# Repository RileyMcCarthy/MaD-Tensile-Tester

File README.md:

# Low Modulus High Speed Tensile Testing Machine

## Purpose

Function as a relatively low cost (< $4,000), portable, spray resistant, user modifiable, open-source uniaxial tensile testing machine for low modulus elastomeric and biologic materials. 

## Physical Specifications

- Strain Rate 0 – 2 m/s

- Force Measurement Range 1 – 10 N

- Gauge Length 10 – 150 mm

- Strain Length 0 – 500 mm

- Data generation rate 1000 sps

## Power Up Sequence

1. Turning on the mains inlet power switch will power the motion control electronics including the “inboard” power on the tensile board 

2. Depressing the on button of the momentary on-off button pair will apply DC power to the machine status switches and ESD chain circuit. 

3. Release of the ESD switch which will apply AC power to the servo controller. 

4. When machine operational and safety criteria are met, motion is affected through operator actuation of the reset function with a control panel and touch screen. 

5. The power down sequence is the reverse of the power up sequence with the off button of the momentary on-off button pair being pressed to remove DC power.

## Operation

The machine state machine operates in three main states with corresponding parameters; 

1. Self Check
- Charge Pump Activated (**ON**/OFF)
2. Machine Check
- Switched Power (**ON**/OFF)
- ESD Travel Limits (**OK**/UPPER FAULT/LOWER FAULT)
- ESD Switch (**ON**/OFF)
- Servo Ready (**YES**/NO)
- Servo Communicating (**YES**/NO)
- Force Gauge Ready (**YES**/NO)
3. Motion
- Mode (Manual or Test)
- Status (DISABLED, ENABLED, SAMPLE LIMIT, MACHINE LIMIT, FAULT)
- Condition (Length, Force, Tension, Compression, Upper Limit, Lower Limit, Door, Stopped, Moving)

## Manual Mode

Manual Operation Mode controls the motor based on user input. The user can selected from the following functions: Off, Incremental Jog, Continuous Jog, Move to Position, Handwheel Jog, Move to Home Position, Set or Move to a Gauge Length, Set or Move to a Force Level and Hold. 

## Test Mode 
Test Mode controls the motor automatically using the functions: Load, Run, Stop Test (Stop Tst) and Hold/Resume.  Motion Profiles are executed by the Run Function. 

** Documentation is a WIP **

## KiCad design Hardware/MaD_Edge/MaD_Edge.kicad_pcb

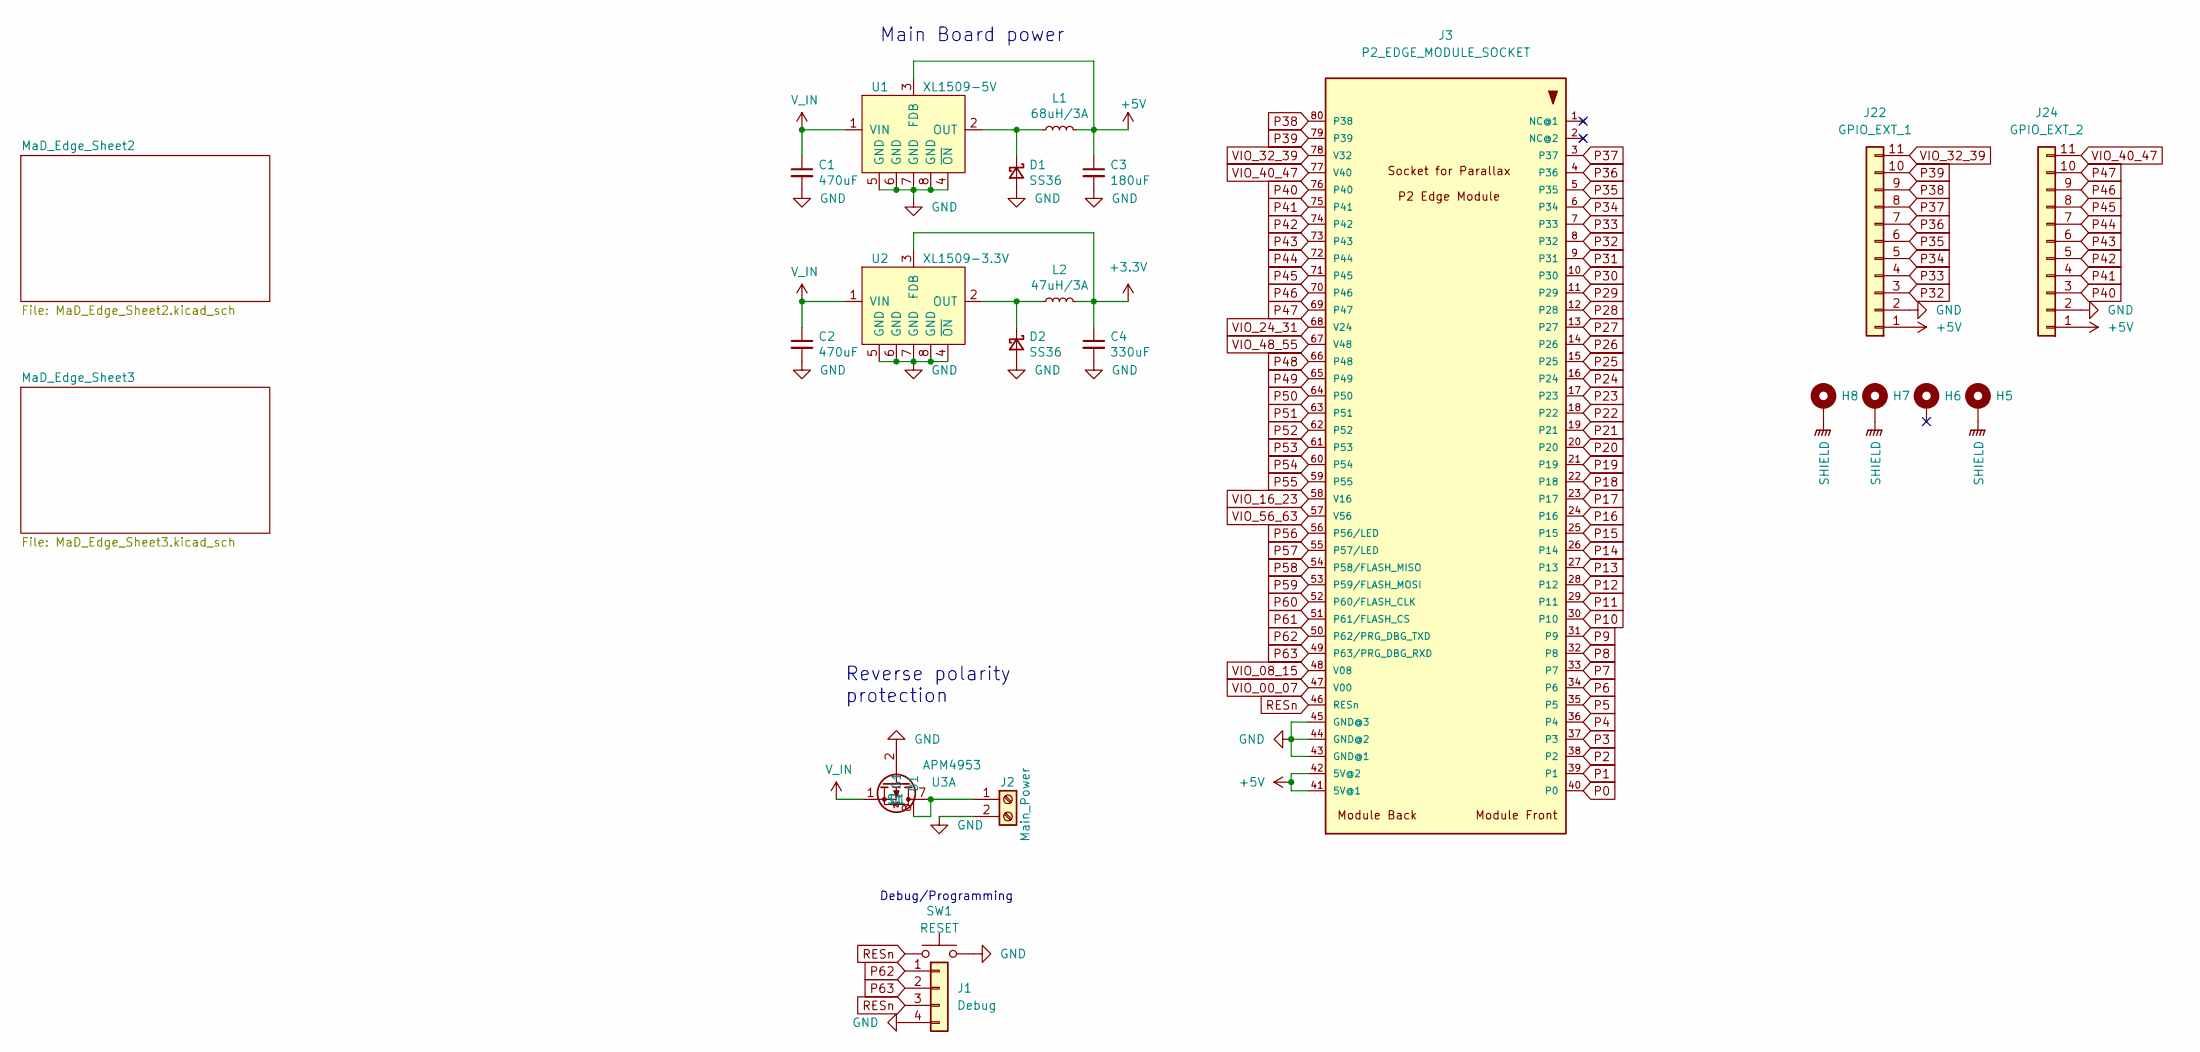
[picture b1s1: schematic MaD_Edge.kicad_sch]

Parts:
C1, C2: 470uF; C_Elec_10x10.2; Manufacturer_Part_Number EEH-ZS1E471P; DIGIKEY 10-EEH-ZS1E471PCT-ND
C3: 180uF; CP_Elec_8x6.9; Manufacturer_Part_Number 25SVPF180M; DIGIKEY P16510CT-ND
C4: 330uF; C_Elec_10x10.2; Manufacturer_Part_Number 25SVPF330M; DIGIKEY P16512CT-ND
D1, D2: SS36; D_SMC; Manufacturer_Part_Number SS36-E3/57T; DIGIKEY SS36-E3/57TGICT-ND
H5, H6, H7, H8: MountingHole_Pad; MountingHole_4mm_Pad; Manufacturer_Part_Number DNP; LCSC DNP
J1: Debug; PinHeader_1x04_P2.54mm_Vertical; Manufacturer_Part_Number DNP; LCSC DNP
J2: Main_Power; 705530106; Manufacturer_Part_Number 0705530106; DIGIKEY WM4153-ND
J3: P2_EDGE_MODULE_SOCKET; Card_Edge_SMT_VERT_1.27mm_80p; Manufacturer_Part_Number 450-00309; LCSC DNP
J22: GPIO_EXT_1; PinHeader_1x11_P1.27mm_Vertical; Manufacturer_Part_Number DNP; LCSC DNP
J24: GPIO_EXT_2; PinHeader_1x11_P1.27mm_Vertical; Manufacturer_Part_Number DNP; LCSC DNP
L1: 68uH/3A; L_10.4x10.4_H4.8; Manufacturer_Part_Number SRP1038A-470M; DIGIKEY SRP1038A-470MCT-ND
L2: 47uH/3A; L_10.4x10.4_H4.8; Manufacturer_Part_Number SLO1365H470MTT; LCSC C149548
SW1: RESET; SW_SPST_PTS645; manufacturer_part_numbe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 PTS645VK31LFS; LCSC C2804591
U1: XL1509-5V; SOP-8_3.9x4.9mm_P1.27mm; Manufacturer_Part_Number XL1509-5.0E1; LCSC C61063
U2: XL1509-3.3V; SOP-8_3.9x4.9mm_P1.27mm; Manufacturer_Part_Number XL1509-3.3E1; LCSC C74193
U3: APM4953; SOP-8_3.9x4.9mm_P1.27mm; Manufacturer_Part_Number APM4953KC-TRG; LCSC C20897

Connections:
+3.3V: C4.1, L2.2, U2.3 (FDB); also elsewhere on the board
+5V: C3.1, J3.41 (5V@1), J3.42 (5V@2), J22.1, J24.1, L1.2, U1.3 (FDB); also elsewhere on the board
GND: C1.2, C2.2, C3.2, C4.2, D1.2 (A), D2.2 (A), J1.4, J2.2, J3.43 (GND@1), J3.44 (GND@2), J3.45 (GND@3), J22.2, J24.2, SW1.2, U1.4 (~ON), U1.5 (GND), U1.6 (GND), U1.7 (GND), U1.8 (GND), U2.4 (~ON), U2.5 (GND), U2.6 (GND), U2.7 (GND), U2.8 (GND), U3.2 (G1); also elsewhere on the board
unnamed: D1.1 (K), L1.1, U1.2 (OUT)
unnamed: D2.1 (K), L2.1, U2.2 (OUT)
unnamed: J2.1, U3.7 (D1), U3.8 (D1)
P0: J3.40 (P0); also elsewhere on the board
P1: J3.39 (P1); also elsewhere on the board
P2: J3.38 (P2); also elsewhere on the board
P3: J3.37 (P3); also elsewhere on the board
P4: J3.36 (P4); also elsewhere on the board
P5: J3.35 (P5); also elsewhere on the board
P6: J3.34 (P6); also elsewhere on the board
P7: J3.33 (P7); also elsewhere on the board
P8: J3.32 (P8); also elsewhere on the board
P9: J3.31 (P9); also elsewhere on the board
P10: J3.30 (P10); also elsewhere on the board
P11: J3.29 (P11); also elsewhere on the board
P12: J3.28 (P12); also elsewhere on the board
P13: J3.27 (P13); also elsewhere on the board
P14: J3.26 (P14); also elsewhere on the board
P15: J3.25 (P15); also elsewhere on the board
P16: J3.24 (P16); also elsewhere on the board
P17: J3.23 (P17); also elsewhere on the board
P18: J3.22 (P18); also elsewhere on the board
P19: J3.21 (P19); also elsewhere on the board
P20: J3.20; also elsewhere on the board
P21: J3.19 (P21); also elsewhere on the board
P22: J3.18 (P22); also elsewhere on the board
P23: J3.17 (P23); also elsewhere on the board
P24: J3.16 (P24); also elsewhere on the board
P25: J3.15 (P25); also elsewhere on the board
P26: J3.14 (P26); also elsewhere on the board
P27: J3.13 (P27); also elsewhere on the board
P28: J3.12 (P28); also elsewhere on the board
P29: J3.11 (P29)
P30: J3.10 (P30)
P31: J3.9 (P31)
P32: J3.8 (P32), J22.3
P33: J3.7 (P33), J22.4
P34: J3.6 (P34), J22.5
P35: J3.5 (P35), J22.6
P36: J3.4 (P36), J22.7
P37: J3.3 (P37), J22.8
P38: J3.80 (P38), J22.9
P39: J3.79 (P39), J22.10
P40: J3.76 (P40), J24.3
P41: J3.75 (P41), J24.4
P42: J3.74 (P42), J24.5
P43: J3.73 (P43), J24.6
P44: J3.72 (P44), J24.7
P45: J3.71 (P45), J24.8
P46: J3.70 (P46), J24.9
P47: J3.69 (P47), J24.10
P48: J3.66 (P48)
P49: J3.65 (P49)
P50: J3.64 (P50)
P51: J3.63 (P51)
P52: J3.62 (P52); also elsewhere on the board
P53: J3.61 (P53); also elsewhere on the board
P54: J3.60 (P54); also elsewhere on the board
P55: J3.59 (P55); also elsewhere on the board
P56: J3.56 (P56/LED)
P57: J3.55 (P57/LED)
P58: J3.54 (P58/FLASH_MISO)
P59: J3.53 (P59/FLASH_MOSI)
P60: J3.52 (P60/FLASH_CLK)
P61: J3.51 (P61/FLASH_CS)
P62: J1.1, J3.50 (P62/PRG_DBG_TXD)
P63: J1.2, J3.49 (P63/PRG_DBG_RXD)
RESn: J1.3, J3.46 (RESn), SW1.1
SHIELD: H5.1, H7.1, H8.1; also elsewhere on the board
VIO_00_07: J3.47 (V00)
VIO_08_15: J3.48 (V08)
VIO_16_23: J3.58 (V16); also elsewhere on the board
VIO_24_31: J3.68 (V24)
VIO_32_39: J3.78 (V32), J22.11
VIO_40_47: J3.77 (V40), J24.11
VIO_48_55: J3.67 (V48)
VIO_56_63: J3.57 (V56)
V_IN: C1.1, C2.1, U1.1 (VIN), U2.1 (VIN), U3.1 (S1)

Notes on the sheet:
Debug/Programming
Main Board power
Reverse polarity protection

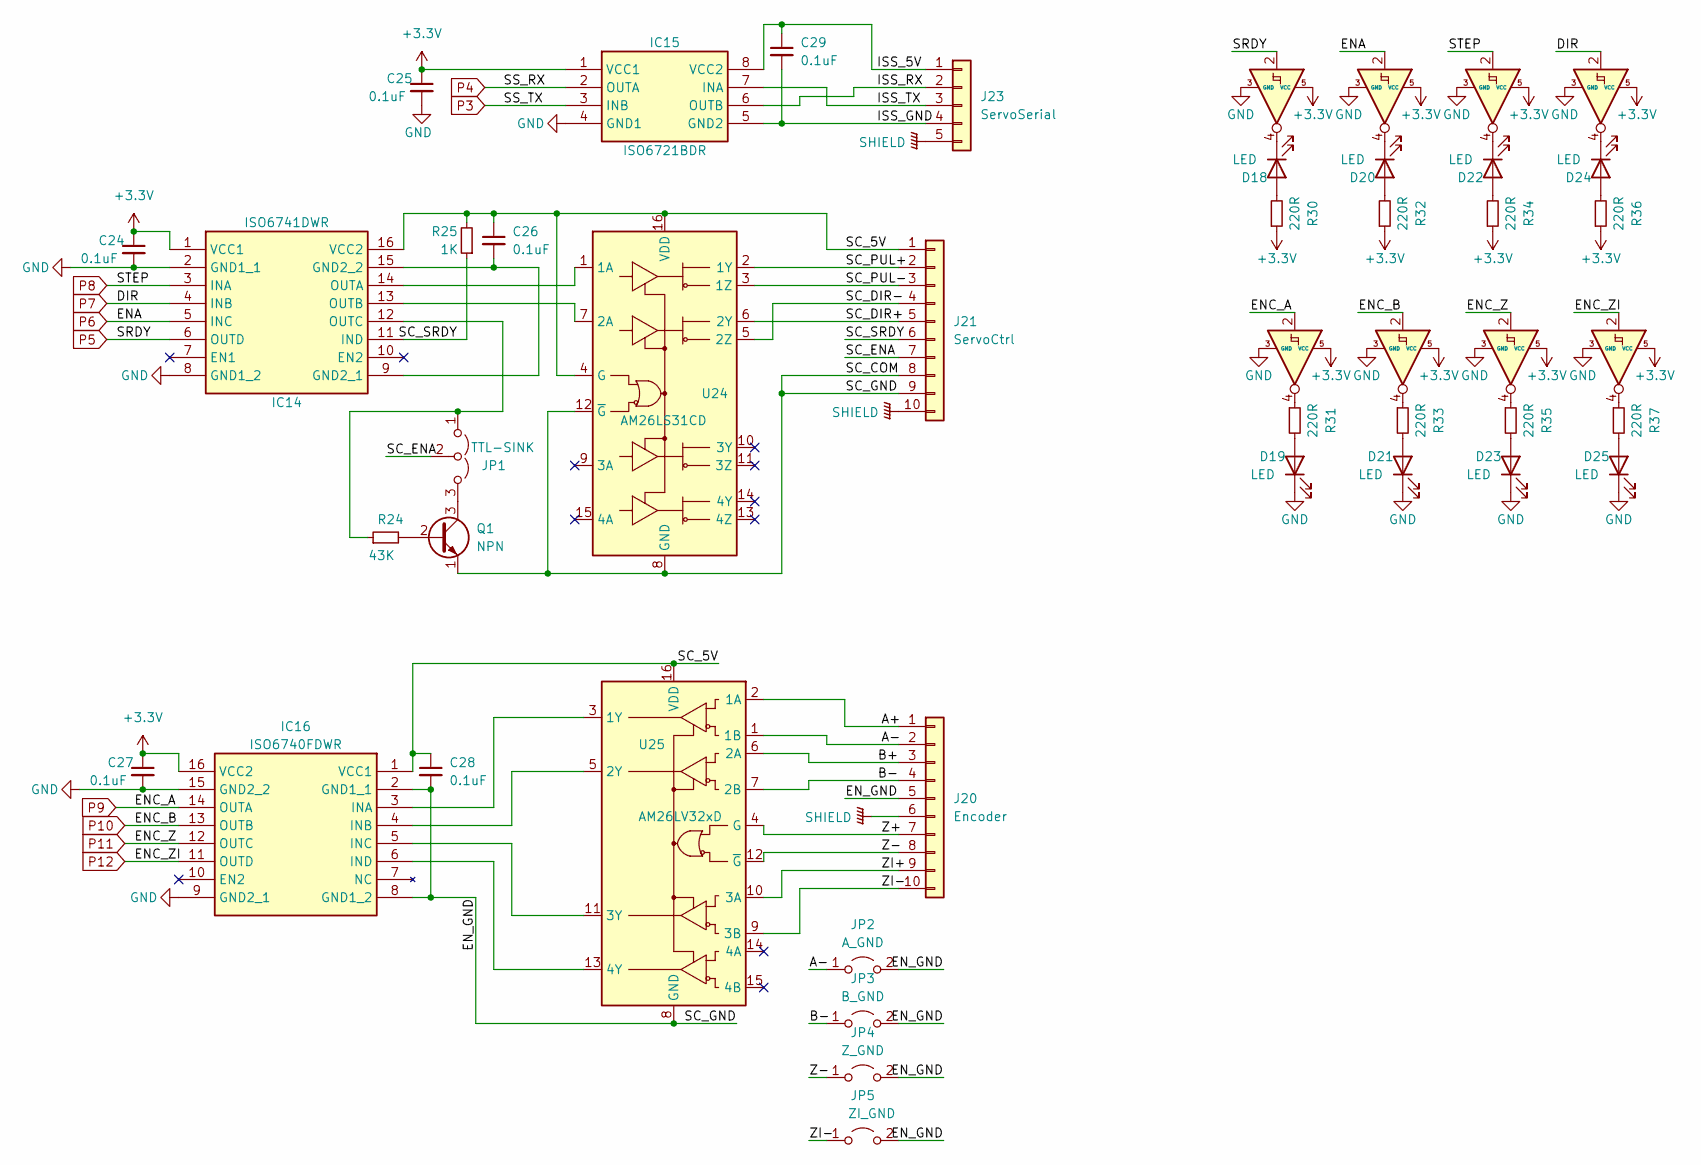
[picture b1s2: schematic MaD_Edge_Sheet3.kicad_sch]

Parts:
C24, C25, C26, C27, C28, C29: 0.1uF; C_0603_1608Metric; Manufacturer_Part_Number CL05A104KA5NNNC; DIGIKEY 1276-1043-1-ND
D18, D19, D20, D21, D22, D23, D24, D25: LED; LED_0603_1608Metric; Manufacturer_Part_Number LTST-C190KGKT; DIGIKEY 160-1435-1-ND
IC14: ISO6741DWR; SOIC127P1030X265-16N; Manufacturer_Part_Number ISO6741DWR; DIGIKEY 296-ISO6741DWRCT-ND
IC15: ISO6721BDR; SOIC127P600X175-8N; Manufacturer_Part_Number ISO6721BDR; DIGIKEY 296-ISO6721BDRCT-ND
IC16: ISO6740FDWR; SOIC127P1030X265-16N; Manufacturer_Part_Number ISO6740DWR; DIGIKEY 296-ISO6740DWRCT-ND
J20: Encoder; Molex_Micro-Fit_3.0_43045-1015_2x05_P3.00mm_Vertical; Manufacturer_Part_Number 0430451015; DIGIKEY WM14304CT-ND
J21: ServoCtrl; Molex_Micro-Fit_3.0_43045-1015_2x05_P3.00mm_Vertical; Manufacturer_Part_Number 0430451015; DIGIKEY WM14304CT-ND
J23: ServoSerial; Molex_Micro-Fit_3.0_43650-0521_1x05_P3.00mm_Vertical; Manufacturer_Part_Number 0436500521; DIGIKEY WM14316CT-ND
JP1: TTL-SINK; PinHeader_1x03_P2.54mm_Vertical; manufacturer_part_numbe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 PZ254V-11-03P; LCSC C2937625
JP2: A_GND; PinHeader_1x02_P2.54mm_Vertical; manufacturer_part_numbe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 PZ254V-11-02P; LCSC C492401
JP3: B_GND; PinHeader_1x02_P2.54mm_Vertical; manufacturer_part_numbe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 PZ254V-11-02P; LCSC C492401
JP4: Z_GND; PinHeader_1x02_P2.54mm_Vertical; manufacturer_part_numbe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 PZ254V-11-02P; LCSC C492401
JP5: ZI_GND; PinHeader_1x02_P2.54mm_Vertical; manufacturer_part_numbe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 PZ254V-11-02P; LCSC C492401
Q1: NPN; TSOT-23; Manufacturer_Part_Number MMBT3904-TP; LCSC C20526
R24: 43K; R_0603_1608Metric; manufacturer_part_numbe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 0603WAF4302T5E; LCSC C23172
R25: 1K; R_0603_1608Metric; manufacturer_part_numbe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 0603WAF1001T5E; LCSC C21190
R30, R31, R32, R33, R34, R35, R36, R37: 220R; R_0603_1608Metric; manufacturer_part_numbe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 0603WAF2200T5E; LCSC C22962
U24: AM26LS31CD; SOIC-16_3.9x9.9mm_P1.27mm; Manufacturer_Part_Number AM26LS31CD; LCSC C6179
U25: AM26LV32xD; SOIC-16_3.9x9.9mm_P1.27mm; Manufacturer_Part_Number AM26LS32CD; LCSC C524786
U27, U28, U29, U30, U31, U32, U33, U34: SN74LVC1G14DBV; SOT-23-5; Manufacturer_Part_Number SN74LVC1G14DBVT; LCSC C5250998

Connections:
+3.3V: C24.1, C25.1, C27.1, IC14.1 (VCC1), IC15.1 (VCC1), IC16.16 (VCC2), R30.1, R32.1, R34.1, R36.1, U27.5 (VCC), U28.5 (VCC), U29.5 (VCC), U30.5 (VCC), U31.5 (VCC), U32.5 (VCC), U33.5 (VCC), U34.5 (VCC); also elsewhere on the board
/MaD_Edge_Sheet3/A+: J20.1, U25.2 (1A)
/MaD_Edge_Sheet3/A-: J20.2, JP2.1 (A), U25.1 (1B)
/MaD_Edge_Sheet3/B+: J20.3, U25.6 (2A)
/MaD_Edge_Sheet3/B-: J20.4, JP3.1 (A), U25.7 (2B)
/MaD_Edge_Sheet3/EN_GND: C28.2, IC16.2 (GND1_1), IC16.8 (GND1_2), J20.5, J21.8, J21.9, JP2.2 (B), JP3.2 (B), JP4.2 (B), JP5.2 (B), Q1.1 (E), U24.8 (GND), U24.12 (~G), U25.8 (GND)
/MaD_Edge_Sheet3/ISS_5V: C29.1, IC15.8 (VCC2), J23.1
/MaD_Edge_Sheet3/ISS_GND: C29.2, IC15.5 (GND2), J23.4
/MaD_Edge_Sheet3/ISS_RX: IC15.6 (OUTB), J23.2
/MaD_Edge_Sheet3/ISS_TX: IC15.7 (INA), J23.3
/MaD_Edge_Sheet3/SC_5V: C26.1, C28.1, IC14.16 (VCC2), IC16.1 (VCC1), J21.1, R25.2, U24.4 (G), U24.16 (VDD), U25.16 (VDD)
/MaD_Edge_Sheet3/SC_DIR+: J21.5, U24.6 (2Y)
/MaD_Edge_Sheet3/SC_DIR-: J21.4, U24.5 (2Z)
/MaD_Edge_Sheet3/SC_ENA: J21.7, JP1.2 (C)
/MaD_Edge_Sheet3/SC_PUL+: J21.2, U24.2 (1Y)
/MaD_Edge_Sheet3/SC_PUL-: J21.3, U24.3 (1Z)
/MaD_Edge_Sheet3/SC_SRDY: IC14.11 (IND), J21.6, R25.1
/MaD_Edge_Sheet3/Z+: J20.7, U25.4 (G)
/MaD_Edge_Sheet3/Z-: J20.8, JP4.1 (A), U25.12 (~G)
/MaD_Edge_Sheet3/ZI+: J20.9, U25.10 (3A)
/MaD_Edge_Sheet3/ZI-: J20.10, JP5.1 (A), U25.9 (3B)
GND: C24.2, C25.2, C27.2, D19.1 (K), D21.1 (K), D23.1 (K), D25.1 (K), IC14.2 (GND1_1), IC14.8 (GND1_2), IC15.4 (GND1), IC16.9 (GND2_1), IC16.15 (GND2_2), U27.3 (GND), U28.3 (GND), U29.3 (GND), U30.3 (GND), U31.3 (GND), U32.3 (GND), U33.3 (GND), U34.3 (GND); also elsewhere on the board
unnamed: C26.2, IC14.9 (GND2_1), IC14.15 (GND2_2)
unnamed: D18.1 (K), U27.4
unnamed: D18.2 (A), R30.2
unnamed: D19.2 (A), R31.2
unnamed: D20.1 (K), U29.4
unnamed: D20.2 (A), R32.2
unnamed: D21.2 (A), R33.2
unnamed: D22.1 (K), U31.4
unnamed: D22.2 (A), R34.2
unnamed: D23.2 (A), R35.2
unnamed: D24.1 (K), U33.4
unnamed: D24.2 (A), R36.2
unnamed: D25.2 (A), R37.2
unnamed: IC14.12 (OUTC), JP1.1 (A), R24.1
unnamed: IC14.13 (OUTB), U24.7 (2A)
unnamed: IC14.14 (OUTA), U24.1 (1A)
unnamed: IC16.3 (INA), U25.3 (1Y)
unnamed: IC16.4 (INB), U25.5 (2Y)
unnamed: IC16.5 (INC), U25.11 (3Y)
unnamed: IC16.6 (IND), U25.13 (4Y)
unnamed: JP1.3 (B), Q1.3 (C)
unnamed: Q1.2 (B), R24.2
unnamed: R31.1, U28.4
unnamed: R33.1, U30.4
unnamed: R35.1, U32.4
unnamed: R37.1, U34.4
P3: IC15.3 (INB); also elsewhere on the board
P4: IC15.2 (OUTA); also elsewhere on the board
P5: IC14.6 (OUTD), U27.2; also elsewhere on the board
P6: IC14.5 (INC), U29.2; also elsewhere on the board
P7: IC14.4 (INB), U33.2; also elsewhere on the board
P8: IC14.3 (INA), U31.2; also elsewhere on the board
P9: IC16.14 (OUTA), U28.2; also elsewhere on the board
P10: IC16.13 (OUTB), U30.2; also elsewhere on the board
P11: IC16.12 (OUTC), U32.2; also elsewhere on the board
P12: IC16.11 (OUTD), U34.2; also elsewhere on the board
SHIELD: J20.6, J21.10, J23.5; also elsewhere on the board

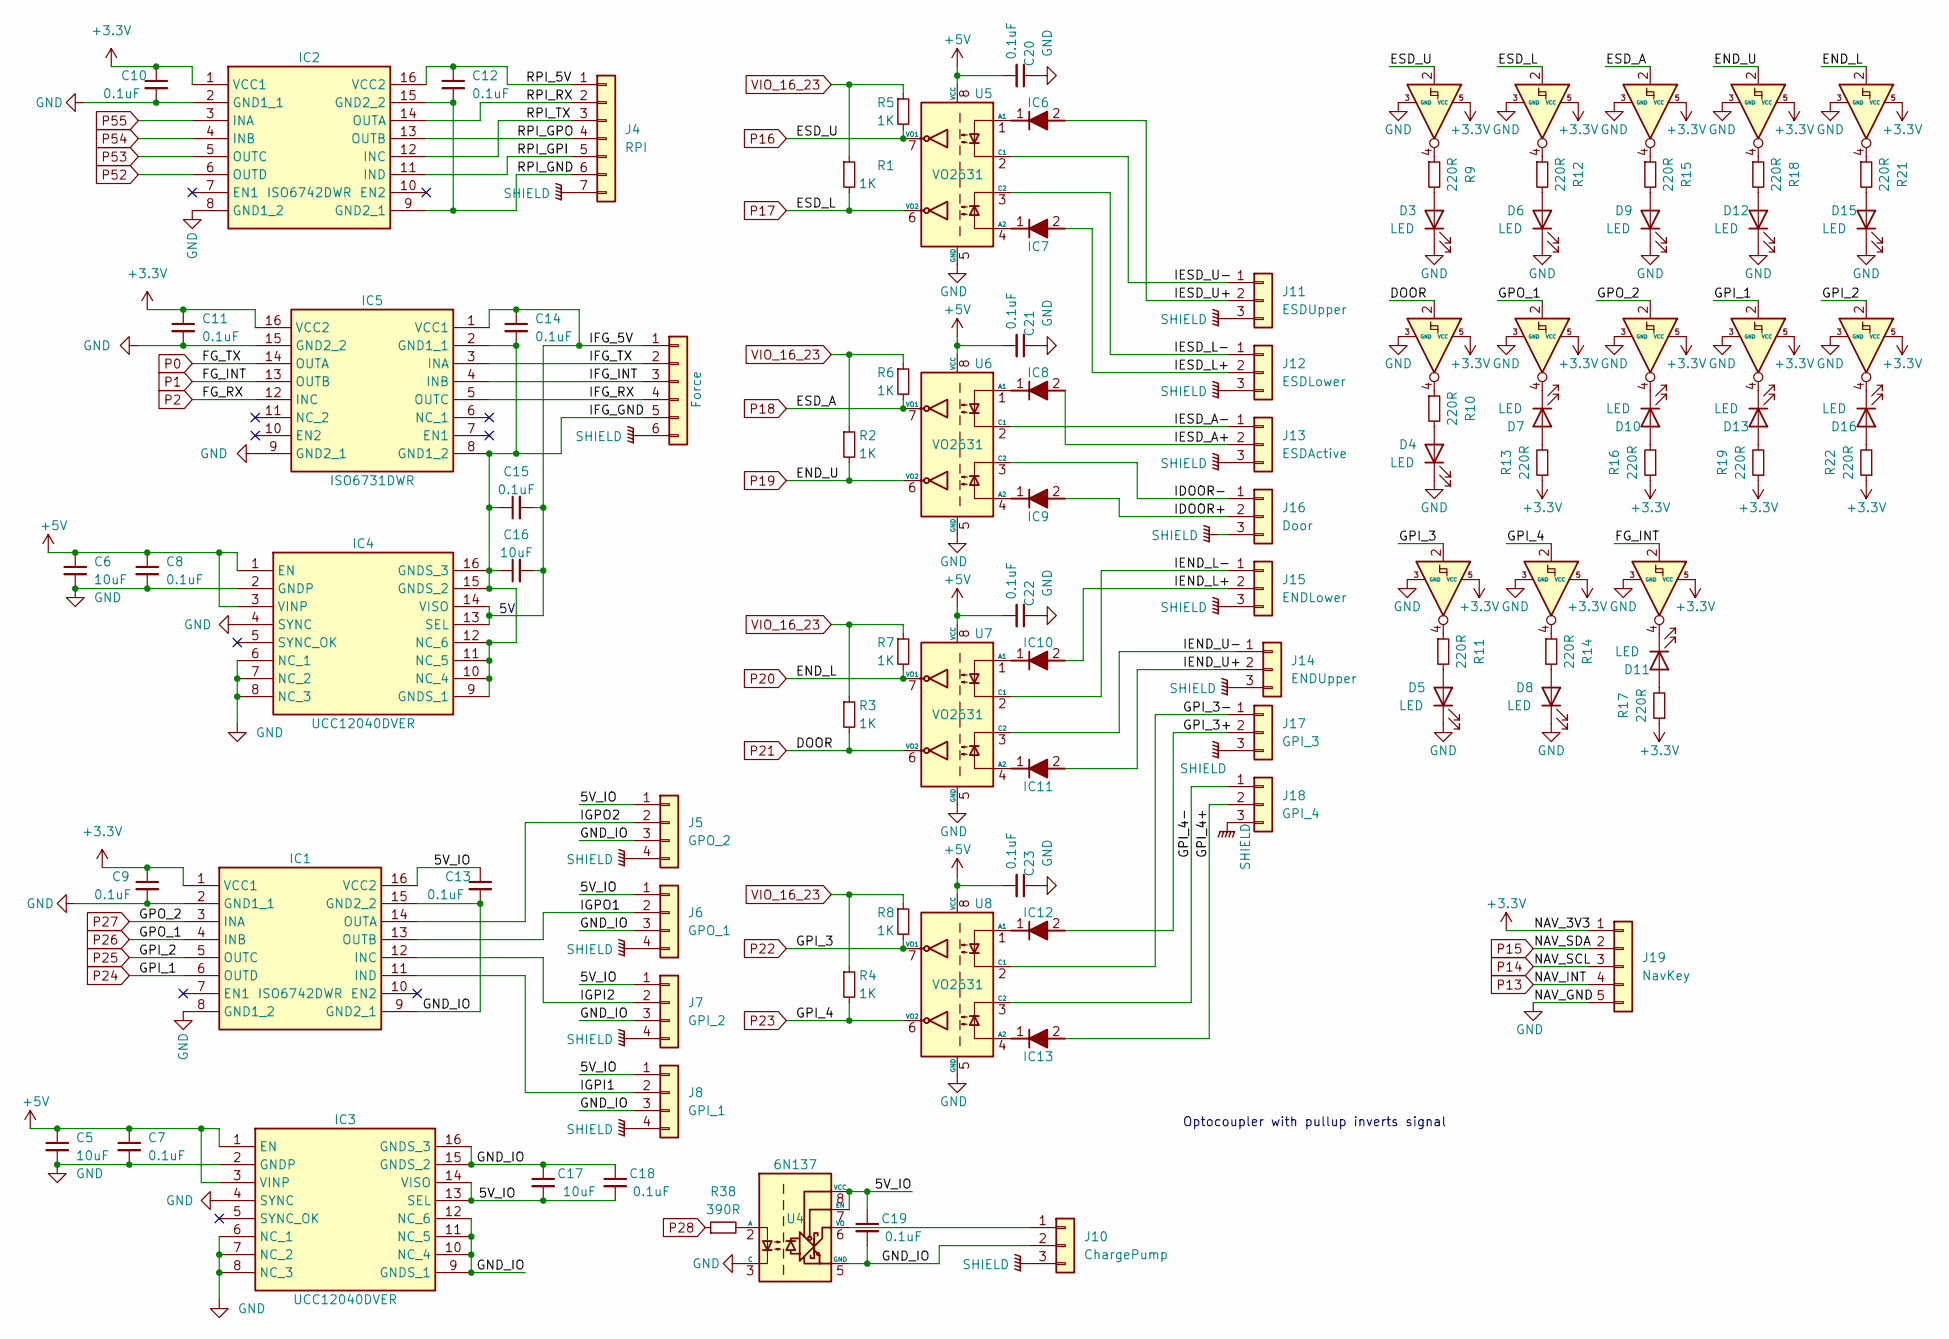
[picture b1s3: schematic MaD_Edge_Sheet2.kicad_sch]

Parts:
C5, C6, C16, C17: 10uF; C_1206_3216Metric; Manufacturer_Part_Number CL31A106MAHNNNE; DIGIKEY 1276-1181-1-ND
C7, C8, C9, C10, C11, C12, C13, C14, C15, C18, C19, C20, C21, C22, C23: 0.1uF; C_0603_1608Metric; Manufacturer_Part_Number CL05A104KA5NNNC; DIGIKEY 1276-1043-1-ND
D3, D4, D5, D6, D7, D8, D9, D10, D11, D12, D13, D15, D16: LED; LED_0603_1608Metric; Manufacturer_Part_Number LTST-C190KGKT; DIGIKEY 160-1435-1-ND
IC1, IC2: ISO6742DWR; SOIC127P1030X265-16N; Manufacturer_Part_Number ISO6742DWR; DIGIKEY 296-ISO6742DWRCT-ND
IC3, IC4: UCC12040DVER; SOIC127P1030X265-16N; Manufacturer_Part_Number UCC12040DVER; DIGIKEY 296-UCC12040DVERCT-ND
IC5: ISO6731DWR; SOIC127P1030X265-16N; Manufacturer_Part_Number ISO6731DWR; DIGIKEY 296-ISO6731DWRCT-ND
IC6, IC7, IC8, IC9, IC10, IC11, IC12, IC13: NSI50010YT1G; SOD3716X135N; Manufacturer_Part_Number NSI50010YT1G; DIGIKEY NSI50010YT1G
J4: RPI; Molex_Micro-Fit_3.0_43045-0618_2x03-1MP_P3.00mm_Vertical; Manufacturer_Part_Number 0430450618; DIGIKEY WM1803CT-ND
J5: GPO_2; Molex_Micro-Fit_3.0_43045-0415_2x02_P3.00mm_Vertical; Manufacturer_Part_Number 0430450415; DIGIKEY WM3251CT-ND
J6: GPO_1; Molex_Micro-Fit_3.0_43045-0415_2x02_P3.00mm_Vertical; Manufacturer_Part_Number 0430450415; DIGIKEY WM3251CT-ND
J7: GPI_2; Molex_Micro-Fit_3.0_43045-0415_2x02_P3.00mm_Vertical; Manufacturer_Part_Number 0430450415; DIGIKEY WM3251CT-ND
J8: GPI_1; Molex_Micro-Fit_3.0_43045-0415_2x02_P3.00mm_Vertical; Manufacturer_Part_Number 0430450415; DIGIKEY WM3251CT-ND
J9: Force; Molex_Micro-Fit_3.0_43045-0615_2x03_P3.00mm_Vertical; Manufacturer_Part_Number 0430450615; DIGIKEY WM6688CT-ND
J10: ChargePump; Molex_Micro-Fit_3.0_43650-0321_1x03_P3.00mm_Vertical; Manufacturer_Part_Number 0436500321; DIGIKEY WM14311CT-ND
J11: ESDUpper; Molex_Micro-Fit_3.0_43650-0321_1x03_P3.00mm_Vertical; Manufacturer_Part_Number 0436500321; DIGIKEY WM14311CT-ND
J12: ESDLower; Molex_Micro-Fit_3.0_43650-0321_1x03_P3.00mm_Vertical; Manufacturer_Part_Number 0436500321; DIGIKEY WM14311CT-ND
J13: ESDActive; Molex_Micro-Fit_3.0_43650-0321_1x03_P3.00mm_Vertical; Manufacturer_Part_Number 0436500321; DIGIKEY WM14311CT-ND
J14: ENDUpper; Molex_Micro-Fit_3.0_43650-0321_1x03_P3.00mm_Vertical; Manufacturer_Part_Number 0436500321; DIGIKEY WM14311CT-ND
J15: ENDLower; Molex_Micro-Fit_3.0_43650-0321_1x03_P3.00mm_Vertical; Manufacturer_Part_Number 0436500321; DIGIKEY WM14311CT-ND
J16: Door; Molex_Micro-Fit_3.0_43650-0321_1x03_P3.00mm_Vertical; Manufacturer_Part_Number 0436500321; DIGIKEY WM14311CT-ND
J17: GPI_3; Molex_Micro-Fit_3.0_43650-0321_1x03_P3.00mm_Vertical; Manufacturer_Part_Number 0436500321; DIGIKEY WM14311CT-ND
J18: GPI_4; Molex_Micro-Fit_3.0_43650-0321_1x03_P3.00mm_Vertical; Manufacturer_Part_Number 0436500321; DIGIKEY WM14311CT-ND
J19: NavKey; Molex_Micro-Fit_3.0_43650-0521_1x05_P3.00mm_Vertical; Manufacturer_Part_Number 0436500521; DIGIKEY WM14316CT-ND
R1, R2, R3, R4, R5, R6, R7, R8: 1K; R_0603_1608Metric; manufacturer_part_numbe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 0603WAF1001T5E; LCSC C21190
R9, R10, R11, R12, R13, R14, R15, R16, R17, R18, R19, R21, R22: 220R; R_0603_1608Metric; manufacturer_part_numbe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 0603WAF2200T5E; LCSC C22962
R38: 390R; R_0603_1608Metric; manufacturer_part_numbe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 0603WAF3900T5E; LCSC C23151
U4: 6N137; DIP-8_W7.62mm; Manufacturer_Part_Number 6N137; LCSC C2904408
U5, U6, U7, U8: VO2631; DIP-8_W7.62mm; Manufacturer_Part_Number VO2631
U9, U10, U11, U12, U13, U14, U15, U16, U17, U18, U19, U21, U22: SN74LVC1G14DBV; SOT-23-5; Manufacturer_Part_Number SN74LVC1G14DBVT; LCSC C5250998

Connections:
+3.3V: C9.1, C10.1, C11.1, IC1.1 (VCC1), IC2.1 (VCC1), IC5.16 (VCC2), J19.1, R13.1, R16.1, R17.1, R19.1, R22.1, U9.5 (VCC), U10.5 (VCC), U11.5 (VCC), U12.5 (VCC), U13.5 (VCC), U14.5 (VCC), U15.5 (VCC), U16.5 (VCC), U17.5 (VCC), U18.5 (VCC), U19.5 (VCC), U21.5 (VCC), U22.5 (VCC); also elsewhere on the board
+5V: C5.1, C6.1, C7.1, C8.1, C20.2, C21.2, C22.2, C23.2, IC3.1 (EN), IC3.3 (VINP), IC4.1 (EN), IC4.3 (VINP), U5.8 (VCC), U6.8 (VCC), U7.8 (VCC), U8.8 (VCC); also elsewhere on the board
/MaD_Edge_Sheet2/5V_IO: C13.1, C17.2, C18.2, C19.1, IC1.16 (VCC2), IC3.13 (SEL), IC3.14 (VISO), J5.1, J6.1, J7.1, J8.1, U4.7 (EN), U4.8 (VCC)
/MaD_Edge_Sheet2/GND_IO: C13.2, C17.1, C18.1, C19.2, IC1.9 (GND2_1), IC1.15 (GND2_2), IC3.9 (GNDS_1), IC3.10 (NC_4), IC3.11 (NC_5), IC3.12 (NC_6), IC3.15 (GNDS_2), IC3.16 (GNDS_3), J5.3, J6.3, J7.3, J8.3, J10.2, U4.5 (GND)
/MaD_Edge_Sheet2/GPI_3+: IC12.2 (A), J17.2
/MaD_Edge_Sheet2/GPI_3-: J17.1, U8.2 (C1)
/MaD_Edge_Sheet2/GPI_4+: IC13.2 (A), J18.2
/MaD_Edge_Sheet2/GPI_4-: J18.1, U8.3 (C2)
/MaD_Edge_Sheet2/IDOOR+: IC9.2 (A), J16.2
/MaD_Edge_Sheet2/IDOOR-: J16.1, U6.3 (C2)
/MaD_Edge_Sheet2/IEND_L+: IC10.2 (A), J15.2
/MaD_Edge_Sheet2/IEND_L-: J15.1, U7.2 (C1)
/MaD_Edge_Sheet2/IEND_U+: IC11.2 (A), J14.2
/MaD_Edge_Sheet2/IEND_U-: J14.1, U7.3 (C2)
/MaD_Edge_Sheet2/IESD_A+: IC8.2 (A), J13.2
/MaD_Edge_Sheet2/IESD_A-: J13.1, U6.2 (C1)
/MaD_Edge_Sheet2/IESD_L+: IC7.2 (A), J12.2
/MaD_Edge_Sheet2/IESD_L-: J12.1, U5.3 (C2)
/MaD_Edge_Sheet2/IESD_U+: IC6.2 (A), J11.2
/MaD_Edge_Sheet2/IESD_U-: J11.1, U5.2 (C1)
/MaD_Edge_Sheet2/IFG_5V: C14.1, C15.2, C16.2, IC4.13 (SEL), IC4.14 (VISO), IC5.1 (VCC1), J9.1
/MaD_Edge_Sheet2/IFG_GND: C14.2, C15.1, C16.1, IC4.9 (GNDS_1), IC4.10 (NC_4), IC4.11 (NC_5), IC4.12 (NC_6), IC4.15 (GNDS_2), IC4.16 (GNDS_3), IC5.2 (GND1_1), IC5.8 (GND1_2), J9.5
/MaD_Edge_Sheet2/IFG_INT: IC5.4 (INB), J9.3
/MaD_Edge_Sheet2/IFG_RX: IC5.5 (OUTC), J9.4
/MaD_Edge_Sheet2/IFG_TX: IC5.3 (INA), J9.2
/MaD_Edge_Sheet2/IGPI1: IC1.11 (IND), J8.2
/MaD_Edge_Sheet2/IGPI2: IC1.12 (INC), J7.2
/MaD_Edge_Sheet2/IGPO1: IC1.13 (OUTB), J6.2
/MaD_Edge_Sheet2/IGPO2: IC1.14 (OUTA), J5.2
/MaD_Edge_Sheet2/RPI_5V: C12.1, IC2.16 (VCC2), J4.1
/MaD_Edge_Sheet2/RPI_GND: C12.2, IC2.9 (GND2_1), IC2.15 (GND2_2), J4.6
/MaD_Edge_Sheet2/RPI_GPI: IC2.11 (IND), J4.5
/MaD_Edge_Sheet2/RPI_GPO: IC2.13 (OUTB), J4.4
/MaD_Edge_Sheet2/RPI_RX: IC2.14 (OUTA), J4.2
/MaD_Edge_Sheet2/RPI_TX: IC2.12 (INC), J4.3
GND: C5.2, C6.2, C7.2, C8.2, C9.2, C10.2, C11.2, C20.1, C21.1, C22.1, C23.1, D3.1 (K), D4.1 (K), D5.1 (K), D6.1 (K), D8.1 (K), D9.1 (K), D12.1 (K), D15.1 (K), IC1.2 (GND1_1), IC1.8 (GND1_2), IC2.2 (GND1_1), IC2.8 (GND1_2), IC3.2 (GNDP), IC3.4 (SYNC), IC3.6 (NC_1), IC3.7 (NC_2), IC3.8 (NC_3), IC4.2 (GNDP), IC4.4 (SYNC), IC4.6 (NC_1), IC4.7 (NC_2), IC4.8 (NC_3), IC5.9 (GND2_1), IC5.15 (GND2_2), J19.5, U4.3 (C), U5.5 (GND), U6.5 (GND), U7.5 (GND), U8.5 (GND), U9.3 (GND), U10.3 (GND), U11.3 (GND), U12.3 (GND), U13.3 (GND), U14.3 (GND), U15.3 (GND), U16.3 (GND), U17.3 (GND), U18.3 (GND), U19.3 (GND), U21.3 (GND), U22.3 (GND); also elsewhere on the board
unnamed: D3.2 (A), R9.2
unnamed: D4.2 (A), R10.2
unnamed: D5.2 (A), R11.2
unnamed: D6.2 (A), R12.2
unnamed: D7.1 (K), U13.4
unnamed: D7.2 (A), R13.2
unnamed: D8.2 (A), R14.2
unnamed: D9.2 (A), R15.2
unnamed: D10.1 (K), U16.4
unnamed: D10.2 (A), R16.2
unnamed: D11.1 (K), U17.4
unnamed: D11.2 (A), R17.2
unnamed: D12.2 (A), R18.2
unnamed: D13.1 (K), U19.4
unnamed: D13.2 (A), R19.2
unnamed: D15.2 (A), R21.2
unnamed: D16.1 (K), U22.4
unnamed: D16.2 (A), R22.2
unnamed: IC6.1 (K), U5.1 (A1)
unnamed: IC7.1 (K), U5.4 (A2)
unnamed: IC8.1 (K), U6.1 (A1)
unnamed: IC9.1 (K), U6.4 (A2)
unnamed: IC10.1 (K), U7.1 (A1)
unnamed: IC11.1 (K), U7.4 (A2)
unnamed: IC12.1 (K), U8.1 (A1)
unnamed: IC13.1 (K), U8.4 (A2)
unnamed: J10.1, U4.6 (VO)
unnamed: R9.1, U9.4
unnamed: R10.1, U10.4
unnamed: R11.1, U11.4
unnamed: R12.1, U12.4
unnamed: R14.1, U14.4
unnamed: R15.1, U15.4
unnamed: R18.1, U18.4
unnamed: R21.1, U21.4
unnamed: R38.2, U4.2 (A)
P0: IC5.14 (OUTA); also elsewhere on the board
P1: IC5.13 (OUTB), U17.2; also elsewhere on the board
P2: IC5.12 (INC); also elsewhere on the board
P13: J19.4; also elsewhere on the board
P14: J19.3; also elsewhere on the board
P15: J19.2; also elsewhere on the board
P16: R5.2, U5.7 (VO1), U9.2; also elsewhere on the board
P17: R1.2, U5.6 (VO2), U12.2; also elsewhere on the board
P18: R6.2, U6.7 (VO1), U15.2; also elsewhere on the board
P19: R2.2, U6.6 (VO2), U18.2; also elsewhere on the board
P20: R7.2, U7.7 (VO1), U21.2; also elsewhere on the board
P21: R3.2, U7.6 (VO2), U10.2; also elsewhere on the board
P22: R8.2, U8.7 (VO1), U11.2; also elsewhere on the board
P23: R4.2, U8.6 (VO2), U14.2; also elsewhere on the board
P24: IC1.6 (OUTD), U19.2; also elsewhere on the board
P25: IC1.5 (OUTC), U22.2; also elsewhere on the board
P26: IC1.4 (INB), U13.2; also elsewhere on the board
P27: IC1.3 (INA), U16.2; also elsewhere on the board
P28: R38.1; also elsewhere on the board
P52: IC2.6 (OUTD); also elsewhere on the board
P53: IC2.5 (OUTC); also elsewhere on the board
P54: IC2.4 (INB); also elsewhere on the board
P55: IC2.3 (INA); also elsewhere on the board
SHIELD: J4.7, J5.4, J6.4, J7.4, J8.4, J9.6, J10.3, J11.3, J12.3, J13.3, J14.3, J15.3, J16.3, J17.3, J18.3; also elsewhere on the board
VIO_16_23: R1.1, R2.1, R3.1, R4.1, R5.1, R6.1, R7.1, R8.1; also elsewhere on the board

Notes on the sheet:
Optocoupler with pullup inverts signal

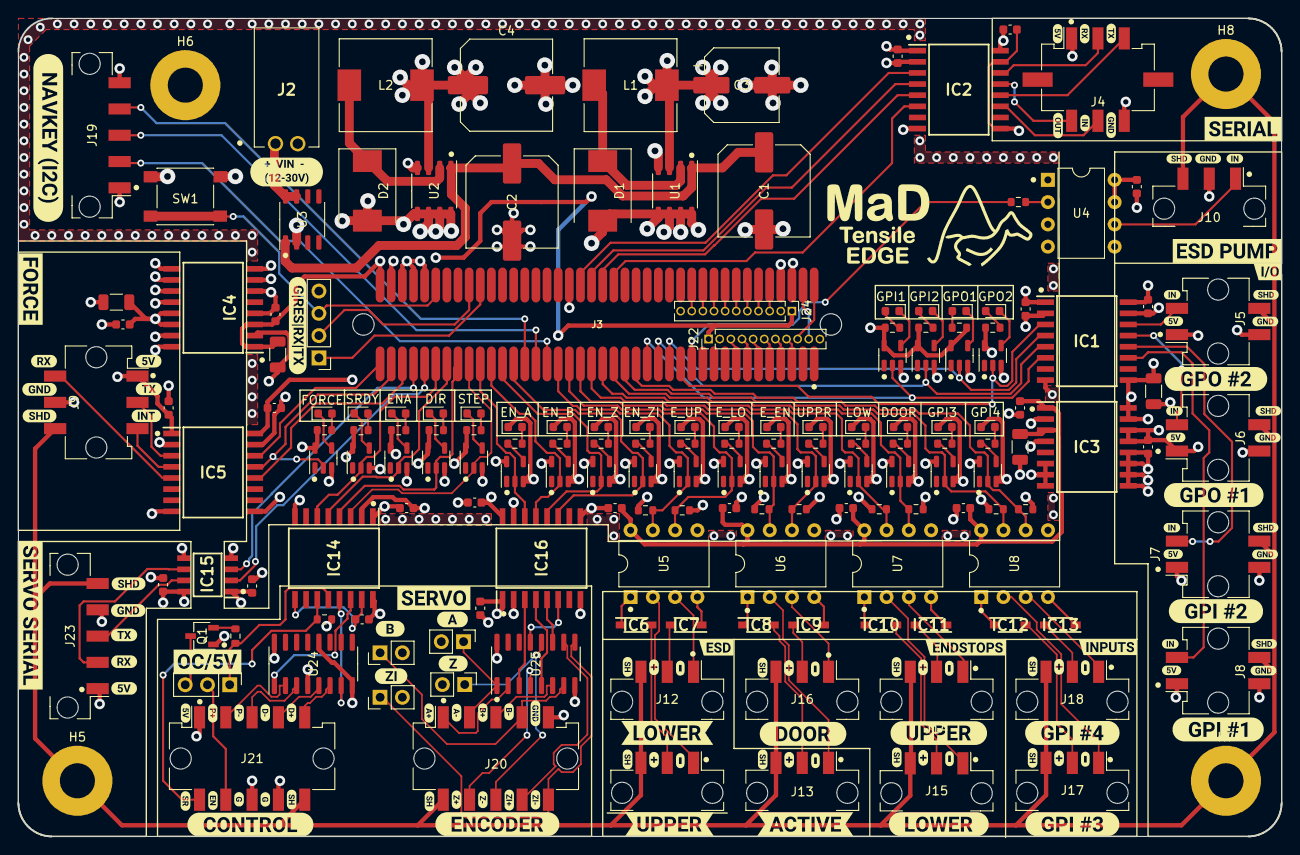
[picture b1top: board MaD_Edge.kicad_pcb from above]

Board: 4 copper layers, 144.1 x 93.3 mm, 279 parts (0 on the bottom side), 178 nets.

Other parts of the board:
kibuzzard-6474CD2A: G***; kibuzzard-6474CD2A
kibuzzard-6474CD43: G***; kibuzzard-6474CD43
kibuzzard-6474CE56: G***; kibuzzard-6474CE56
kibuzzard-6474CEBE: G***; kibuzzard-6474CEBE
kibuzzard-6474CEDF: G***; kibuzzard-6474CEDF
kibuzzard-6474CEEB: G***; kibuzzard-6474CEEB
kibuzzard-6474CF4E: G***; kibuzzard-6474CF4E
kibuzzard-6474CF37: G***; kibuzzard-6474CF37
kibuzzard-6474D1C6: G***; kibuzzard-6474D1C6
kibuzzard-6474D2B0: G***; kibuzzard-6474D2B0
kibuzzard-6474D2C7: G***; kibuzzard-6474D2C7
kibuzzard-6474D2DE: G***; kibuzzard-6474D2DE
kibuzzard-6474D3A4: G***; kibuzzard-6474D3A4
kibuzzard-6474D3B5: G***; kibuzzard-6474D3B5
kibuzzard-6474D3C7: G***; kibuzzard-6474D3C7
kibuzzard-6474D3D9: G***; kibuzzard-6474D3D9
kibuzzard-6474D10F: G***; kibuzzard-6474D10F
kibuzzard-6474D11D: G***; kibuzzard-6474D11D
kibuzzard-6474D12A: G***; kibuzzard-6474D12A
kibuzzard-6474D26F: G***; kibuzzard-6474D26F
kibuzzard-6474D36B: G***; kibuzzard-6474D36B
kibuzzard-6474D37E: G***; kibuzzard-6474D37E
kibuzzard-6474D215: G***; kibuzzard-6474D215
kibuzzard-6474D298: G***; kibuzzard-6474D298
kibuzzard-64776FD8: G***; kibuzzard-64776FD8
kibuzzard-647770C7, kibuzzard-647770C7#2: G***; kibuzzard-647770C7
kibuzzard-647770D0: G***; kibuzzard-647770D0
kibuzzard-647770D6: G***; kibuzzard-647770D6
kibuzzard-647771C1: G***; kibuzzard-647771C1
kibuzzard-647772E1: G***; kibuzzard-647772E1
kibuzzard-647772FA: G***; kibuzzard-647772FA
kibuzzard-647774DE: G***; kibuzzard-647774DE
kibuzzard-647775A2: G***; kibuzzard-647775A2
kibuzzard-647777A9, kibuzzard-647777A9#2, kibuzzard-647777A9#3, kibuzzard-647777A9#4: G***; kibuzzard-647777A9
kibuzzard-647777B2, kibuzzard-647777B2#2, kibuzzard-647777B2#3, kibuzzard-647777B2#4: G***; kibuzzard-647777B2
kibuzzard-647778CC: G***; kibuzzard-647778CC
kibuzzard-647778DF: G***; kibuzzard-647778DF
kibuzzard-647778EA: G***; kibuzzard-647778EA
kibuzzard-6477707F: G***; kibuzzard-6477707F
kibuzzard-6477708A: G***; kibuzzard-6477708A
kibuzzard-6477713B: G***; kibuzzard-6477713B
kibuzzard-6477715F: G***; kibuzzard-6477715F
kibuzzard-6477723E: G***; kibuzzard-6477723E
kibuzzard-6477742A: G***; kibuzzard-6477742A
kibuzzard-6477743C: G***; kibuzzard-6477743C
kibuzzard-6477745C: G***; kibuzzard-6477745C
kibuzzard-6477746F: G***; kibuzzard-6477746F
kibuzzard-6477757D: G***; kibuzzard-6477757D
kibuzzard-6477779F, kibuzzard-6477779F#2, kibuzzard-6477779F#3, kibuzzard-6477779F#4: G***; kibuzzard-6477779F
kibuzzard-6477790B: G***; kibuzzard-6477790B
kibuzzard-64777084: G***; kibuzzard-64777084
kibuzzard-64777131: G***; kibuzzard-64777131
kibuzzard-64777136: G***; kibuzzard-64777136
kibuzzard-64777256: G***; kibuzzard-64777256
kibuzzard-64777263: G***; kibuzzard-64777263
kibuzzard-64777279: G***; kibuzzard-64777279
kibuzzard-64777285: G***; kibuzzard-64777285
kibuzzard-64777339, kibuzzard-64777339#2: G***; kibuzzard-64777339
kibuzzard-64777365, kibuzzard-64777365#2: G***; kibuzzard-64777365
kibuzzard-64777421: G***; kibuzzard-64777421
kibuzzard-64777448: G***; kibuzzard-64777448
kibuzzard-64777463: G***; kibuzzard-64777463
kibuzzard-64777469: G***; kibuzzard-64777469
kibuzzard-64777566: G***; kibuzzard-64777566
kibuzzard-64777573: G***; kibuzzard-64777573
kibuzzard-64777588: G***; kibuzzard-64777588
kibuzzard-64777629, kibuzzard-64777629#2, kibuzzard-64777629#3, kibuzzard-64777629#4, kibuzzard-64777629#5, kibuzzard-64777629#6, kibuzzard-64777629#7, kibuzzard-64777629#8: G***; kibuzzard-64777629
kibuzzard-64777654, kibuzzard-64777654#2, kibuzzard-64777654#3, kibuzzard-64777654#4, kibuzzard-64777654#5, kibuzzard-64777654#6, kibuzzard-64777654#7, kibuzzard-64777654#8: G***; kibuzzard-64777654
kibuzzard-64777688, kibuzzard-64777688#2, kibuzzard-64777688#3, kibuzzard-64777688#4, kibuzzard-64777688#5, kibuzzard-64777688#6, kibuzzard-64777688#7, kibuzzard-64777688#8: G***; kibuzzard-64777688
kibuzzard-64777781, kibuzzard-64777781#2, kibuzzard-64777781#3, kibuzzard-64777781#4: G***; kibuzzard-64777781
kibuzzard-64777814: G***; kibuzzard-64777814
kibuzzard-64777822: G***; kibuzzard-64777822
kibuzzard-64777848: G***; kibuzzard-64777848
kibuzzard-64777917: G***; kibuzzard-64777917
kibuzzard-64777922: G***; kibuzzard-64777922
